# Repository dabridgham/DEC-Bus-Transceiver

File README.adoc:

= DEC Bus Transceiver Ideas

Experiments in looking for a circuit that could perform the function
of a bus transceiver for the DEC busses (Unibus and QBUS).

For the moment, this is a place to jot down ideas but if it were to be
carried through, the idea would be to build a small test board to try
out the transceiver circuit on real busses to see that it works.

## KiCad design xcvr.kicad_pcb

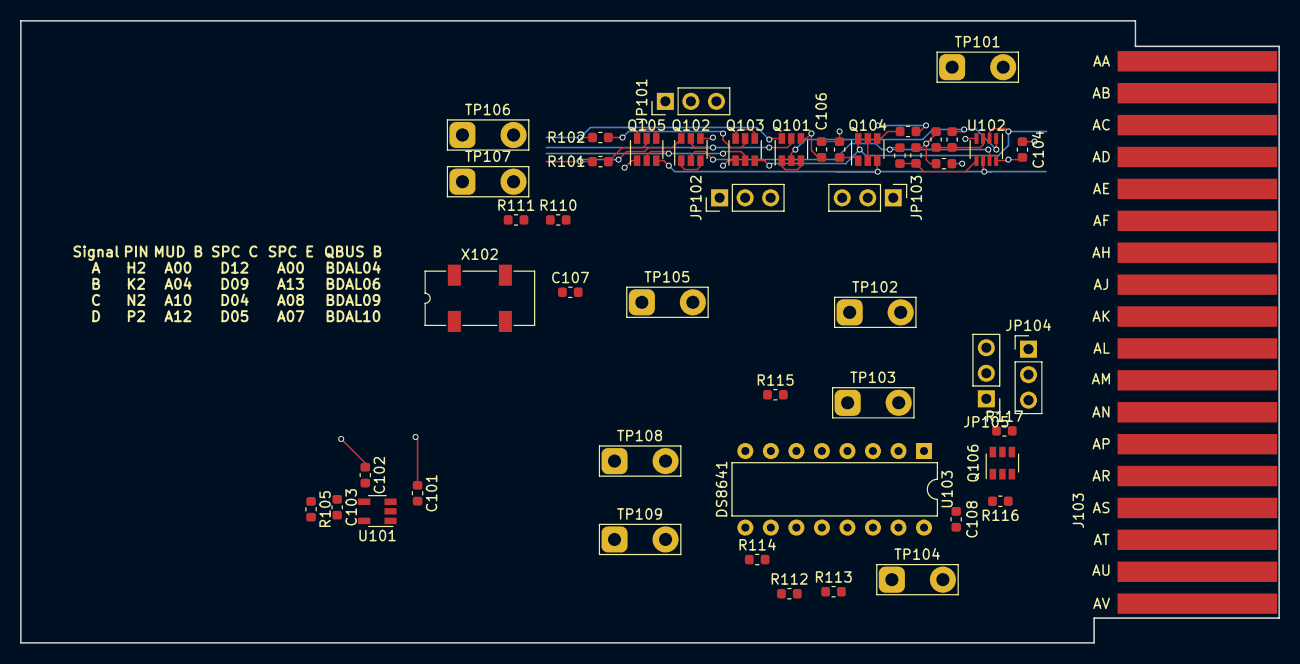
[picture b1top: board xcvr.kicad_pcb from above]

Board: 4 copper layers, 125.2 x 61.9 mm, 50 parts (0 on the bottom side), 34 nets.

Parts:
C101, C105, C106: 1uF; C_0603_1608Metric
C102: 10nF; C_0603_1608Metric
C103: 10uF; C_0603_1608Metric
C104, C107, C108: 100nF; C_0603_1608Metric
J103: QBUS_B; DEC_Edge_Fingers_single_height
JP101, JP102, JP103, JP104, JP105: Jumper_3_Bridged12; PinHeader_1x03_P2.54mm_Vertical
Q101, Q102, Q103, Q105: Dual_NMOS; SOT-23-6
Q104, Q106: PMOS; SOT-23-6
R101, R102: ??; R_0603_1608Metric
R103, R104: 6.8k; R_0603_1608Metric
R105: .15mA for each line; R_0603_1608Metric
R106, R107: 22k; R_0603_1608Metric
R108, R109, R116, R117: 120; R_0603_1608Metric
R110, R111: 10k; R_0603_1608Metric
R112, R113, R114, R115: 4.7k; R_0603_1608Metric
TP101, TP102, TP103, TP104, TP105, TP106, TP107, TP108, TP109: B0; TestPoint_2Pads_Pitch5.08mm_Drill1.3mm
U101: LT1761-1.2; TSOT-23-5
U102: MAX9107; SOT-23-8
U103: DS8641; DIP-16_W7.62mm
X102: SG-636PCE 5MHz; Oscillator_SMD_SeikoEpson_SG8002JC-4Pin_10.5x5.0mm

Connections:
/3V3: C107.1, JP101.3, JP102.1, JP103.3, R110.1, R111.1, X102.4
/5V0: C101.1, C104.1, C108.1, J103.A2, U101.1, U101.3, U102.8, U103.16
/A: J103.H2, Q103.3, Q104.6, TP101.1, TP101.2, U102.2
/B: J103.K2, JP104.1, JP105.3, TP102.1, TP102.2
/B1: JP104.2, Q104.3, Q105.3, U102.6
/B2: JP105.2, Q106.6, U103.1
/B3: J103.P2, Q106.3, TP104.1, TP104.2, U103.15
/C: J103.N2, JP104.3, JP105.1, TP103.1, TP103.2
/OSC: Q101.6, Q102.6, R101.1, R102.1, R110.2, R111.2, R112.2, R113.2, TP106.1, TP106.2, TP107.1, TP107.2, U103.2, U103.14, X102.3
/R2: TP108.1, TP108.2, U103.3
/R3: TP109.1, TP109.2, U103.13
/RX: JP101.2, Q101.5, Q102.5
/TERM: JP103.2, Q104.2, Q104.5, Q106.2, Q106.5
/TX: JP102.2, Q103.2, Q105.2
/V_term: C106.1, R108.1, R109.1, R116.1, R117.1
/Vref: C102.1, C103.1, C105.1, R105.1, R106.2, R107.2, U101.5
GND: C101.2, C103.2, C104.2, C105.2, C106.2, C107.2, C108.2, J103.C2, JP101.1, JP102.3, JP103.1, Q101.4, Q102.4, Q103.1, Q105.1, R105.2, R112.1, R113.1, R114.1, R115.1, TP105.1, TP105.2, U101.2, U102.4, U103.8, X102.2
unnamed: C102.2, U101.4
unnamed: Q101.1, Q101.3
unnamed: Q101.2, R104.1, U102.1
unnamed: Q102.1, Q102.3
unnamed: Q102.2, R103.1, U102.7
unnamed: Q103.4, Q103.6
unnamed: Q103.5, R102.2
unnamed: Q104.1, R108.2
unnamed: Q104.4, R109.2
unnamed: Q105.4, Q105.6
unnamed: Q105.5, R101.2
unnamed: Q106.1, R116.2
unnamed: Q106.4, R117.2
unnamed: R103.2, R106.1, U102.5
unnamed: R104.2, R107.1, U102.3
unnamed: R114.2, U103.11
unnamed: R115.2, U103.5

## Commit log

2025-03-30 Initial commit to get the files up to GitHub. Still very much in the "doodling" stage at this point.
2025-03-30 More explanation
2025-03-30 For people who don't have KiCad.
2025-03-30 Added the discrete comparator circuit
